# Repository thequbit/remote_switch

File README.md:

remote_switch
=============

schematic and board layout for wireless 12v switching relays.

This is for a specific project, but it can be adapted to be used to switch any (4) 12v sources from (4) 5v sources.

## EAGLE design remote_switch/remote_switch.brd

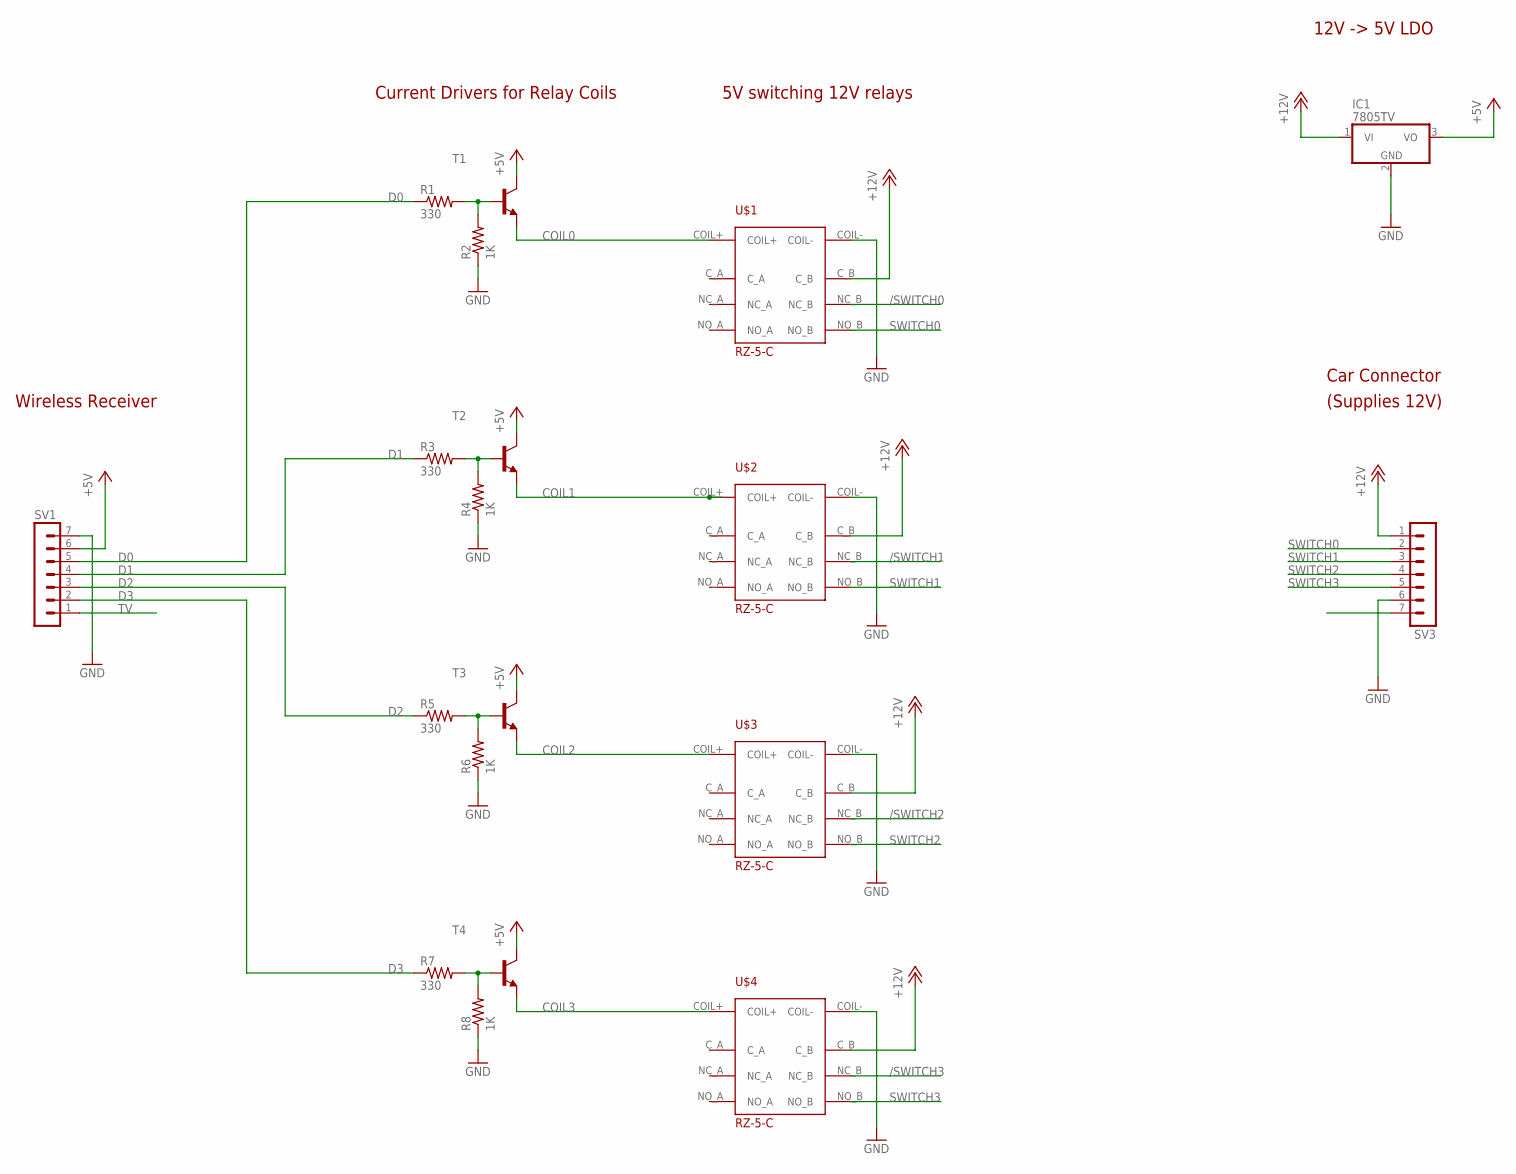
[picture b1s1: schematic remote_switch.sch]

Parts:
IC1: 7805TV; TO220V
R1, R3, R5, R7: 330; P0613V
R2, R4, R6, R8: 1K; P0613V
SV1, SV3: MA07-1
T1, T2, T3, T4: MPS2222A-NPN-TO92-CBE; TO92-CBE
U$1, U$2, U$3, U$4: RZ-5-C

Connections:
+5V: IC1.3 (VO), SV1.6, T1.C, T2.C, T3.C, T4.C
+12V: IC1.1 (VI), SV3.1, U$1.C_B, U$2.C_B, U$3.C_B, U$4.C_B
/SWITCH0: U$1.NC_B
/SWITCH1: U$2.NC_B
/SWITCH2: U$3.NC_B
/SWITCH3: U$4.NC_B
COIL0: T1.E, U$1.COIL+
COIL1: T2.E, U$2.COIL+
COIL2: T3.E, U$3.COIL+
COIL3: T4.E, U$4.COIL+
D0: R1.1, SV1.5
D1: R3.1, SV1.4
D2: R5.1, SV1.3
D3: R7.1, SV1.2
GND: IC1.2 (GND), R2.1, R4.1, R6.1, R8.1, SV1.7, SV3.6, U$1.COIL-, U$2.COIL-, U$3.COIL-, U$4.COIL-
unnamed: R1.2, R2.2, T1.B
unnamed: R3.2, R4.2, T2.B
unnamed: R5.2, R6.2, T3.B
unnamed: R7.2, R8.2, T4.B
SWITCH0: SV3.2, U$1.NO_B
SWITCH1: SV3.3, U$2.NO_B
SWITCH2: SV3.4, U$3.NO_B
SWITCH3: SV3.5, U$4.NO_B
TV: SV1.1

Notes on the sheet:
Wireless Receiver
Current Drivers for Relay Coils
5V switching 12V relays
12V -> 5V LDO
Car Connector
(Supplies 12V)

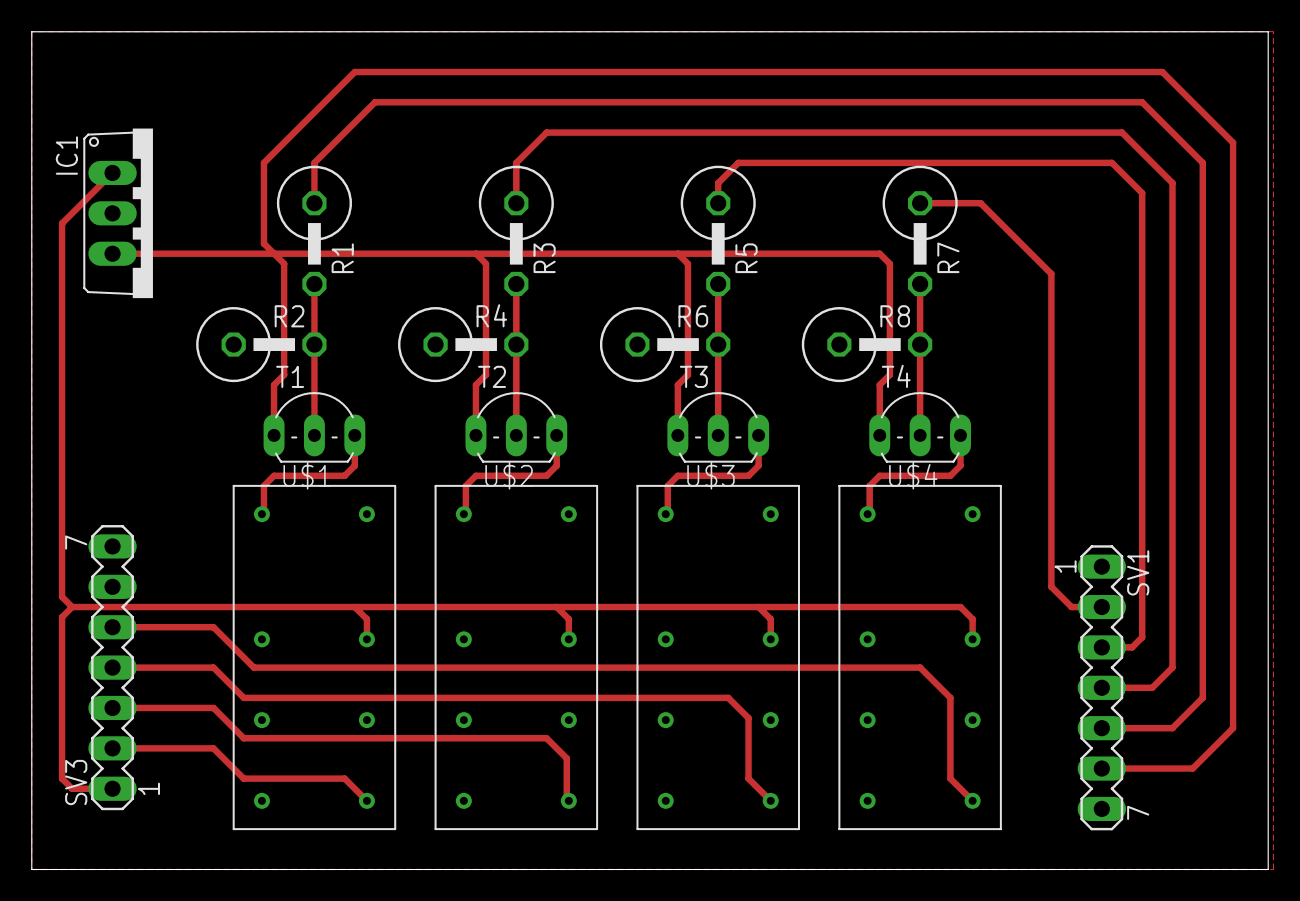
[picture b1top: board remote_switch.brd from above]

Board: 2 copper layers, 77.8 x 52.7 mm, 19 parts (0 on the bottom side), 19 nets.

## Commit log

2013-04-13 library with the RZ-5C relay in it
2013-04-13 first rev of the schematic
2013-04-13 first rev of the board layout - not space optomized at all, but I did get it to about 3" x 2"
2013-04-13 eagle project file
2013-04-13 pdf's of the board and schematic - NOTE: THESE MAY BE OUT OF DATE FROM FROM THE SOURCE FILES!!!!!
2013-04-13 images of the breadboard version of the project
2013-04-13 simple readme
